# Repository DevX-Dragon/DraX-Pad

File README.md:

# **🎮 DraX Pad**
The Ultimate Programmable Macro Pad

Welcome to the DraX Pad project! This is a high-performance, compact macro pad designed for productivity, gaming, and custom control. Powered by the XIAO RP2040, it packs a ton of features into a tiny footprint.

## ✨ Key Features
**⌨️ 10 Programmable Keys:** Fully customizable to launch apps, run complex macros, or control your media.

**⚡ Hot-Swappable:** Change your mechanical switches on the fly—no soldering required.

**📺 0.96" OLED Display:** Real-time feedback, system stats, or even play games directly on your pad using the macro keys.

**🌈 RGB Backlit:** Full per-key RGB lighting for that perfect aesthetic.

**🧠 XIAO RP2040 Powered:** Dual-core ARM Cortex M0+ processor for lightning-fast response times.

**🔌 USB-C Connectivity:** Modern, reliable, and easy to plug in.

**🎛️ Multiple Presets:** Switch between different layers (Gaming, Video Editing, Coding) with a single tap.

## Images (Layouts)

## Images (Case Render)

## Components Needed

| Component | Quantity | Description |
| :--- | :---: | :--- |
| **Macropad PCB** | 1 | The main circuit board that includes the SK6812 leds (neopixels), diodes, capacitors|
| **Mechanical Switches** | 10 | Cherry MX compatible (3x3 layout + 1 on top left) |
| **Keycaps** | 10 | Any Profiles |
| **Microcontroller** | 1 | Seed Studio Xiao RP2040 or simillar |
| **USB-C Cable** | 1 | Data-capable cable (not just charging) |

> This is a project done for [Hack Club Blueprint Program](https://blueprint.hackclub.com/home)

> Feel free to make your own version and post it online!

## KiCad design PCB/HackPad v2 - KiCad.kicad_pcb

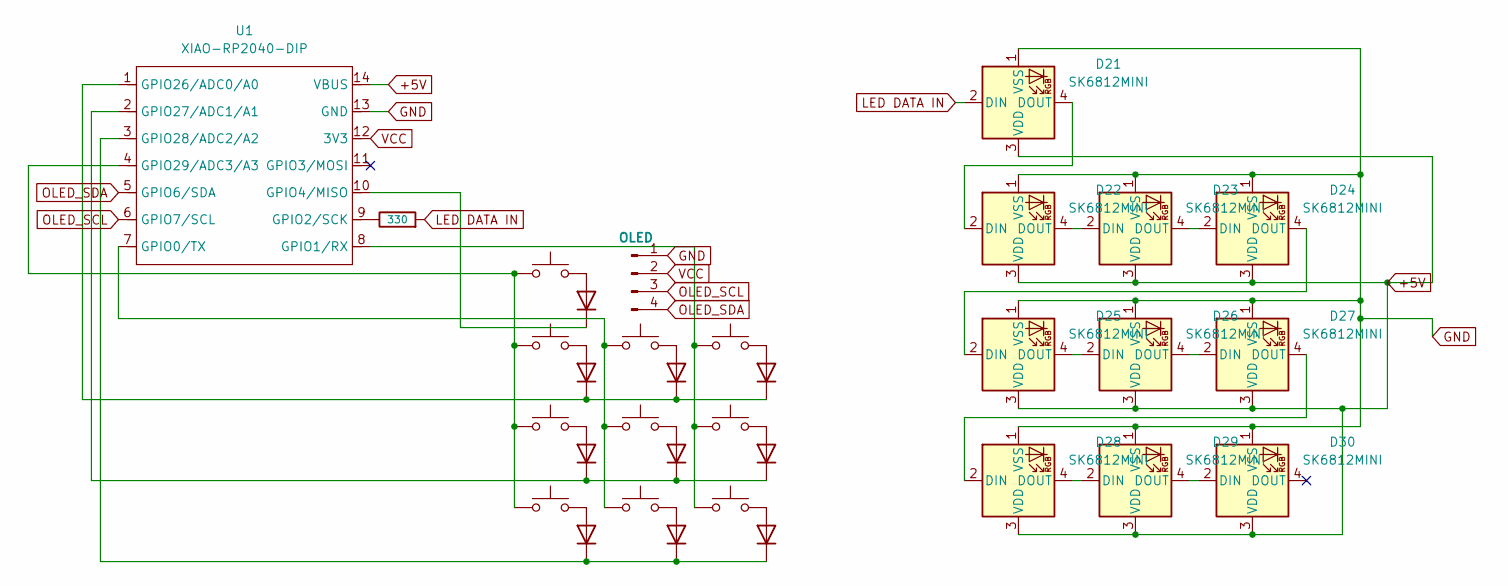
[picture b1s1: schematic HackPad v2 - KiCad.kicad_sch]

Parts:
D1, D2, D3, D4, D5, D6, D7, D8, D9, D10: D; D_DO-35_SOD27_P7.62mm_Horizontal
D21, D22, D23, D24, D25, D26, D27, D28, D29, D30: SK6812MINI; MX_SK6812MINI-E
J1: OLED; 128x64OLED
R1: 330; R_Axial_DIN0204_L3.6mm_D1.6mm_P7.62mm_Horizontal
SW1, SW2, SW3, SW4, SW5, SW6, SW7, SW8, SW9, SW10: SW_Push; SW_Cherry_MX_1.00u_PCB
U1: XIAO-RP2040-DIP

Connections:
+5V: D21.3 (VDD), D22.3 (VDD), D23.3 (VDD), D24.3 (VDD), D25.3 (VDD), D26.3 (VDD), D27.3 (VDD), D28.3 (VDD), D29.3 (VDD), D30.3 (VDD), U1.14 (VBUS)
GND: D21.1 (VSS), D22.1 (VSS), D23.1 (VSS), D24.1 (VSS), D25.1 (VSS), D26.1 (VSS), D27.1 (VSS), D28.1 (VSS), D29.1 (VSS), D30.1 (VSS), J1.1, U1.13 (GND)
LED DATA IN: D21.2 (DIN), R1.2
unnamed: D1.2 (A), SW1.2
unnamed: D1.1 (K), D2.1 (K), D3.1 (K), U1.1 (GPIO26/ADC0/A0)
unnamed: D2.2 (A), SW2.2
unnamed: D3.2 (A), SW3.2
unnamed: D4.2 (A), SW6.2
unnamed: D4.1 (K), D5.1 (K), D6.1 (K), U1.2 (GPIO27/ADC1/A1)
unnamed: D5.2 (A), SW5.2
unnamed: D6.2 (A), SW4.2
unnamed: D7.2 (A), SW9.2
unnamed: D7.1 (K), D8.1 (K), D9.1 (K), U1.3 (GPIO28/ADC2/A2)
unnamed: D8.2 (A), SW8.2
unnamed: D9.2 (A), SW7.2
unnamed: D10.2 (A), SW10.2
unnamed: D10.1 (K), U1.10 (GPIO4/MISO)
unnamed: D21.4 (DOUT), D22.2 (DIN)
unnamed: D22.4 (DOUT), D23.2 (DIN)
unnamed: D23.4 (DOUT), D24.2 (DIN)
unnamed: D24.4 (DOUT), D25.2 (DIN)
unnamed: D25.4 (DOUT), D26.2 (DIN)
unnamed: D26.4 (DOUT), D27.2 (DIN)
unnamed: D27.4 (DOUT), D28.2 (DIN)
unnamed: D28.4 (DOUT), D29.2 (DIN)
unnamed: D29.4 (DOUT), D30.2 (DIN)
unnamed: SW2.1, SW5.1, SW8.1, U1.7 (GPIO0/TX)
unnamed: SW3.1, SW6.1, SW9.1, U1.8 (GPIO1/RX)
unnamed: R1.1, U1.9 (GPIO2/SCK)
unnamed: SW1.1, SW4.1, SW7.1, SW10.1, U1.4 (GPIO29/ADC3/A3)
OLED_SCL: J1.3, U1.6 (GPIO7/SCL)
OLED_SDA: J1.4, U1.5 (GPIO6/SDA)
VCC: J1.2, U1.12 (3V3)

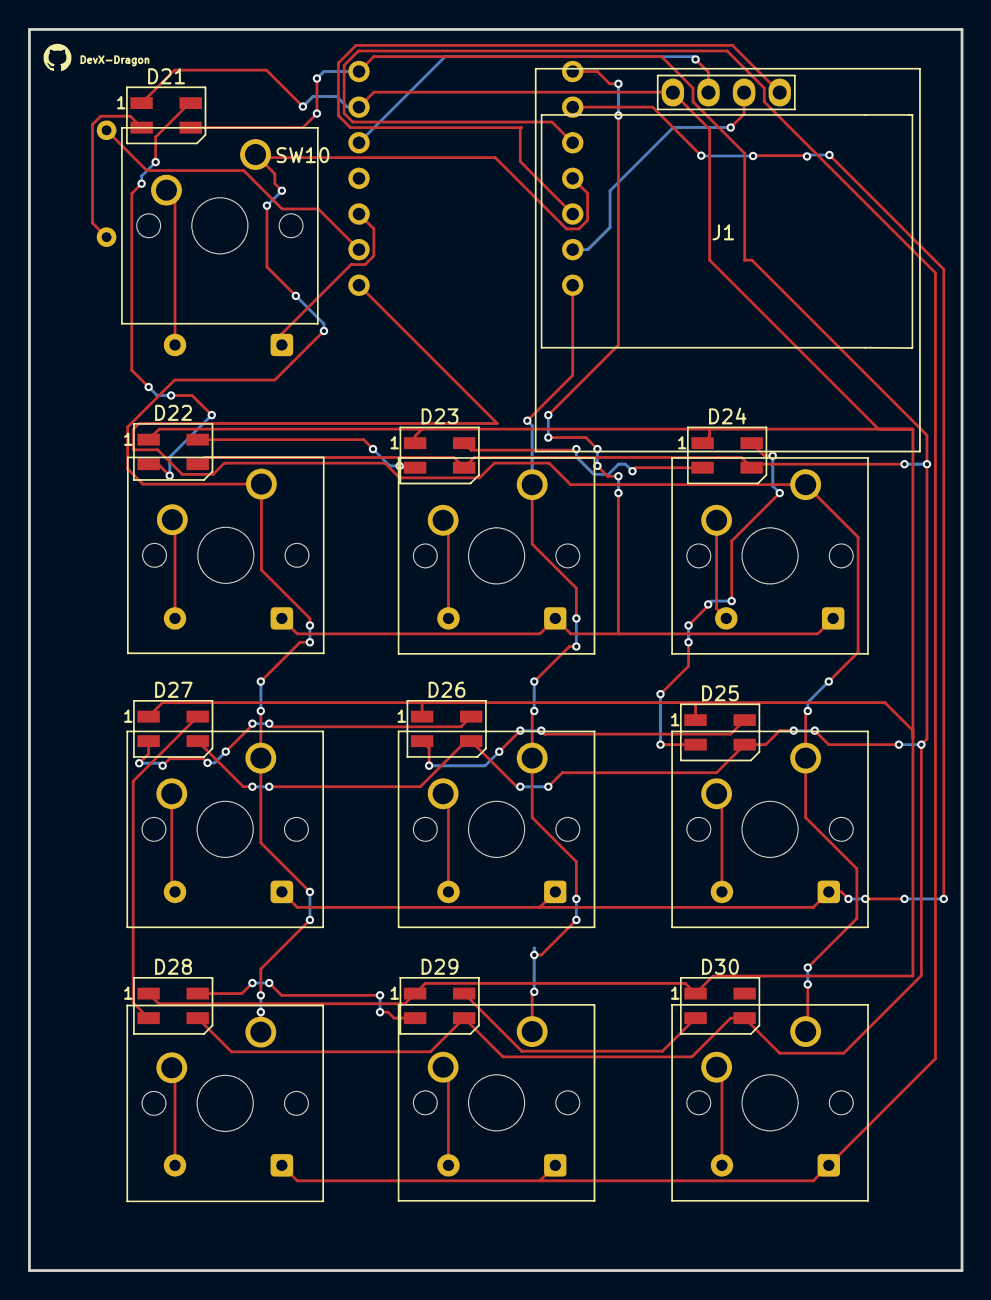
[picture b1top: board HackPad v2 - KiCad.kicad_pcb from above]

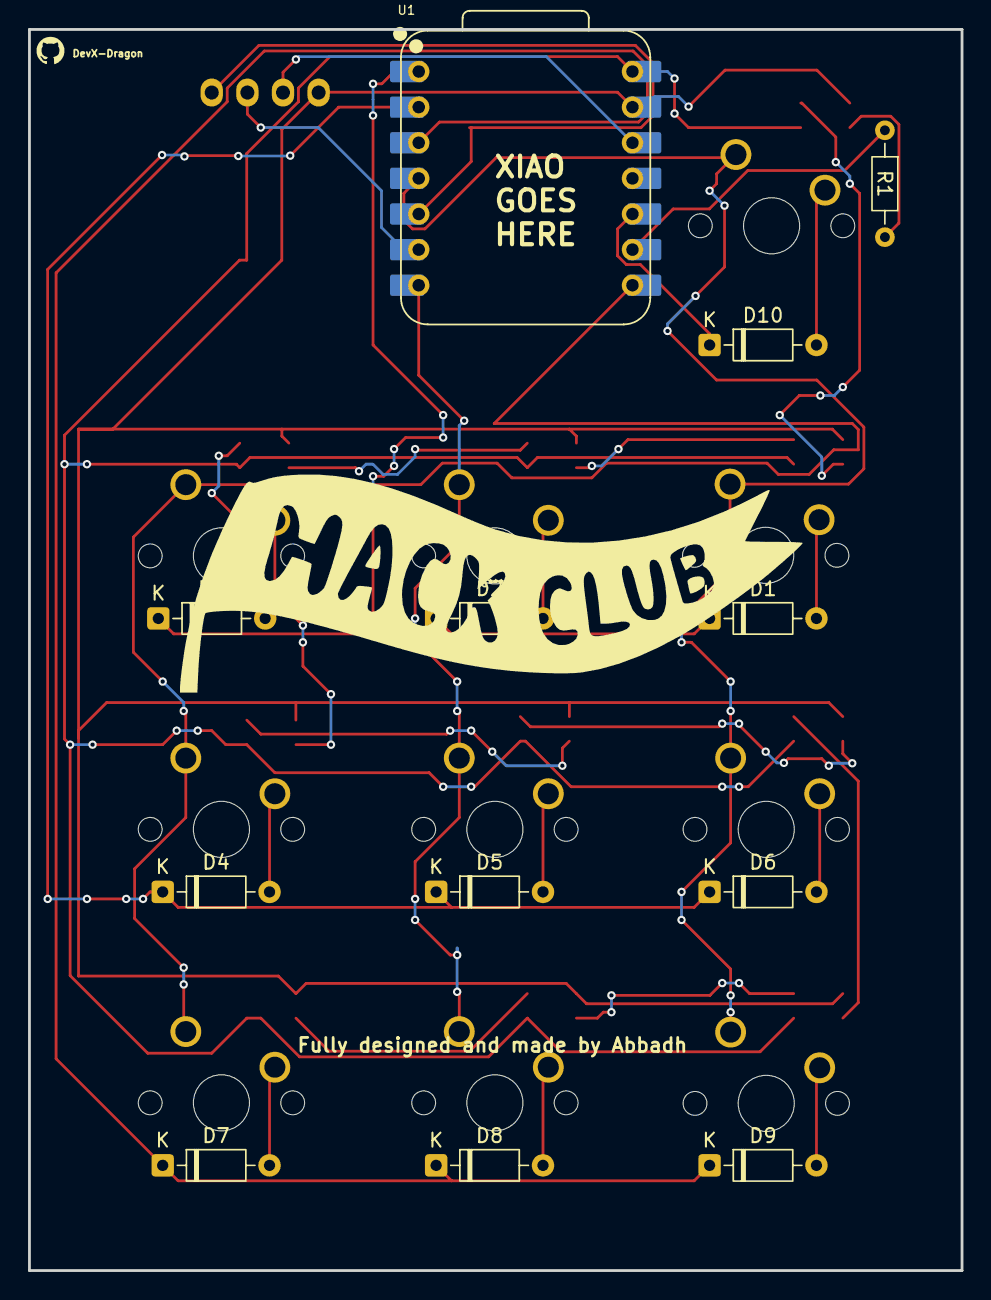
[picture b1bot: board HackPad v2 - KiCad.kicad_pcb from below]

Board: 2 copper layers, 66.5 x 88.5 mm, 33 parts (12 on the bottom side), 33 nets.

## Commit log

2025-12-30 Rename qww1.png to plain-one.png
2025-12-30 Rename wb side .png to 3D render .png
2025-12-30 Rename wb.png to render with PCB visible.png
2025-12-30 Create test
2025-12-30 adding case renders
